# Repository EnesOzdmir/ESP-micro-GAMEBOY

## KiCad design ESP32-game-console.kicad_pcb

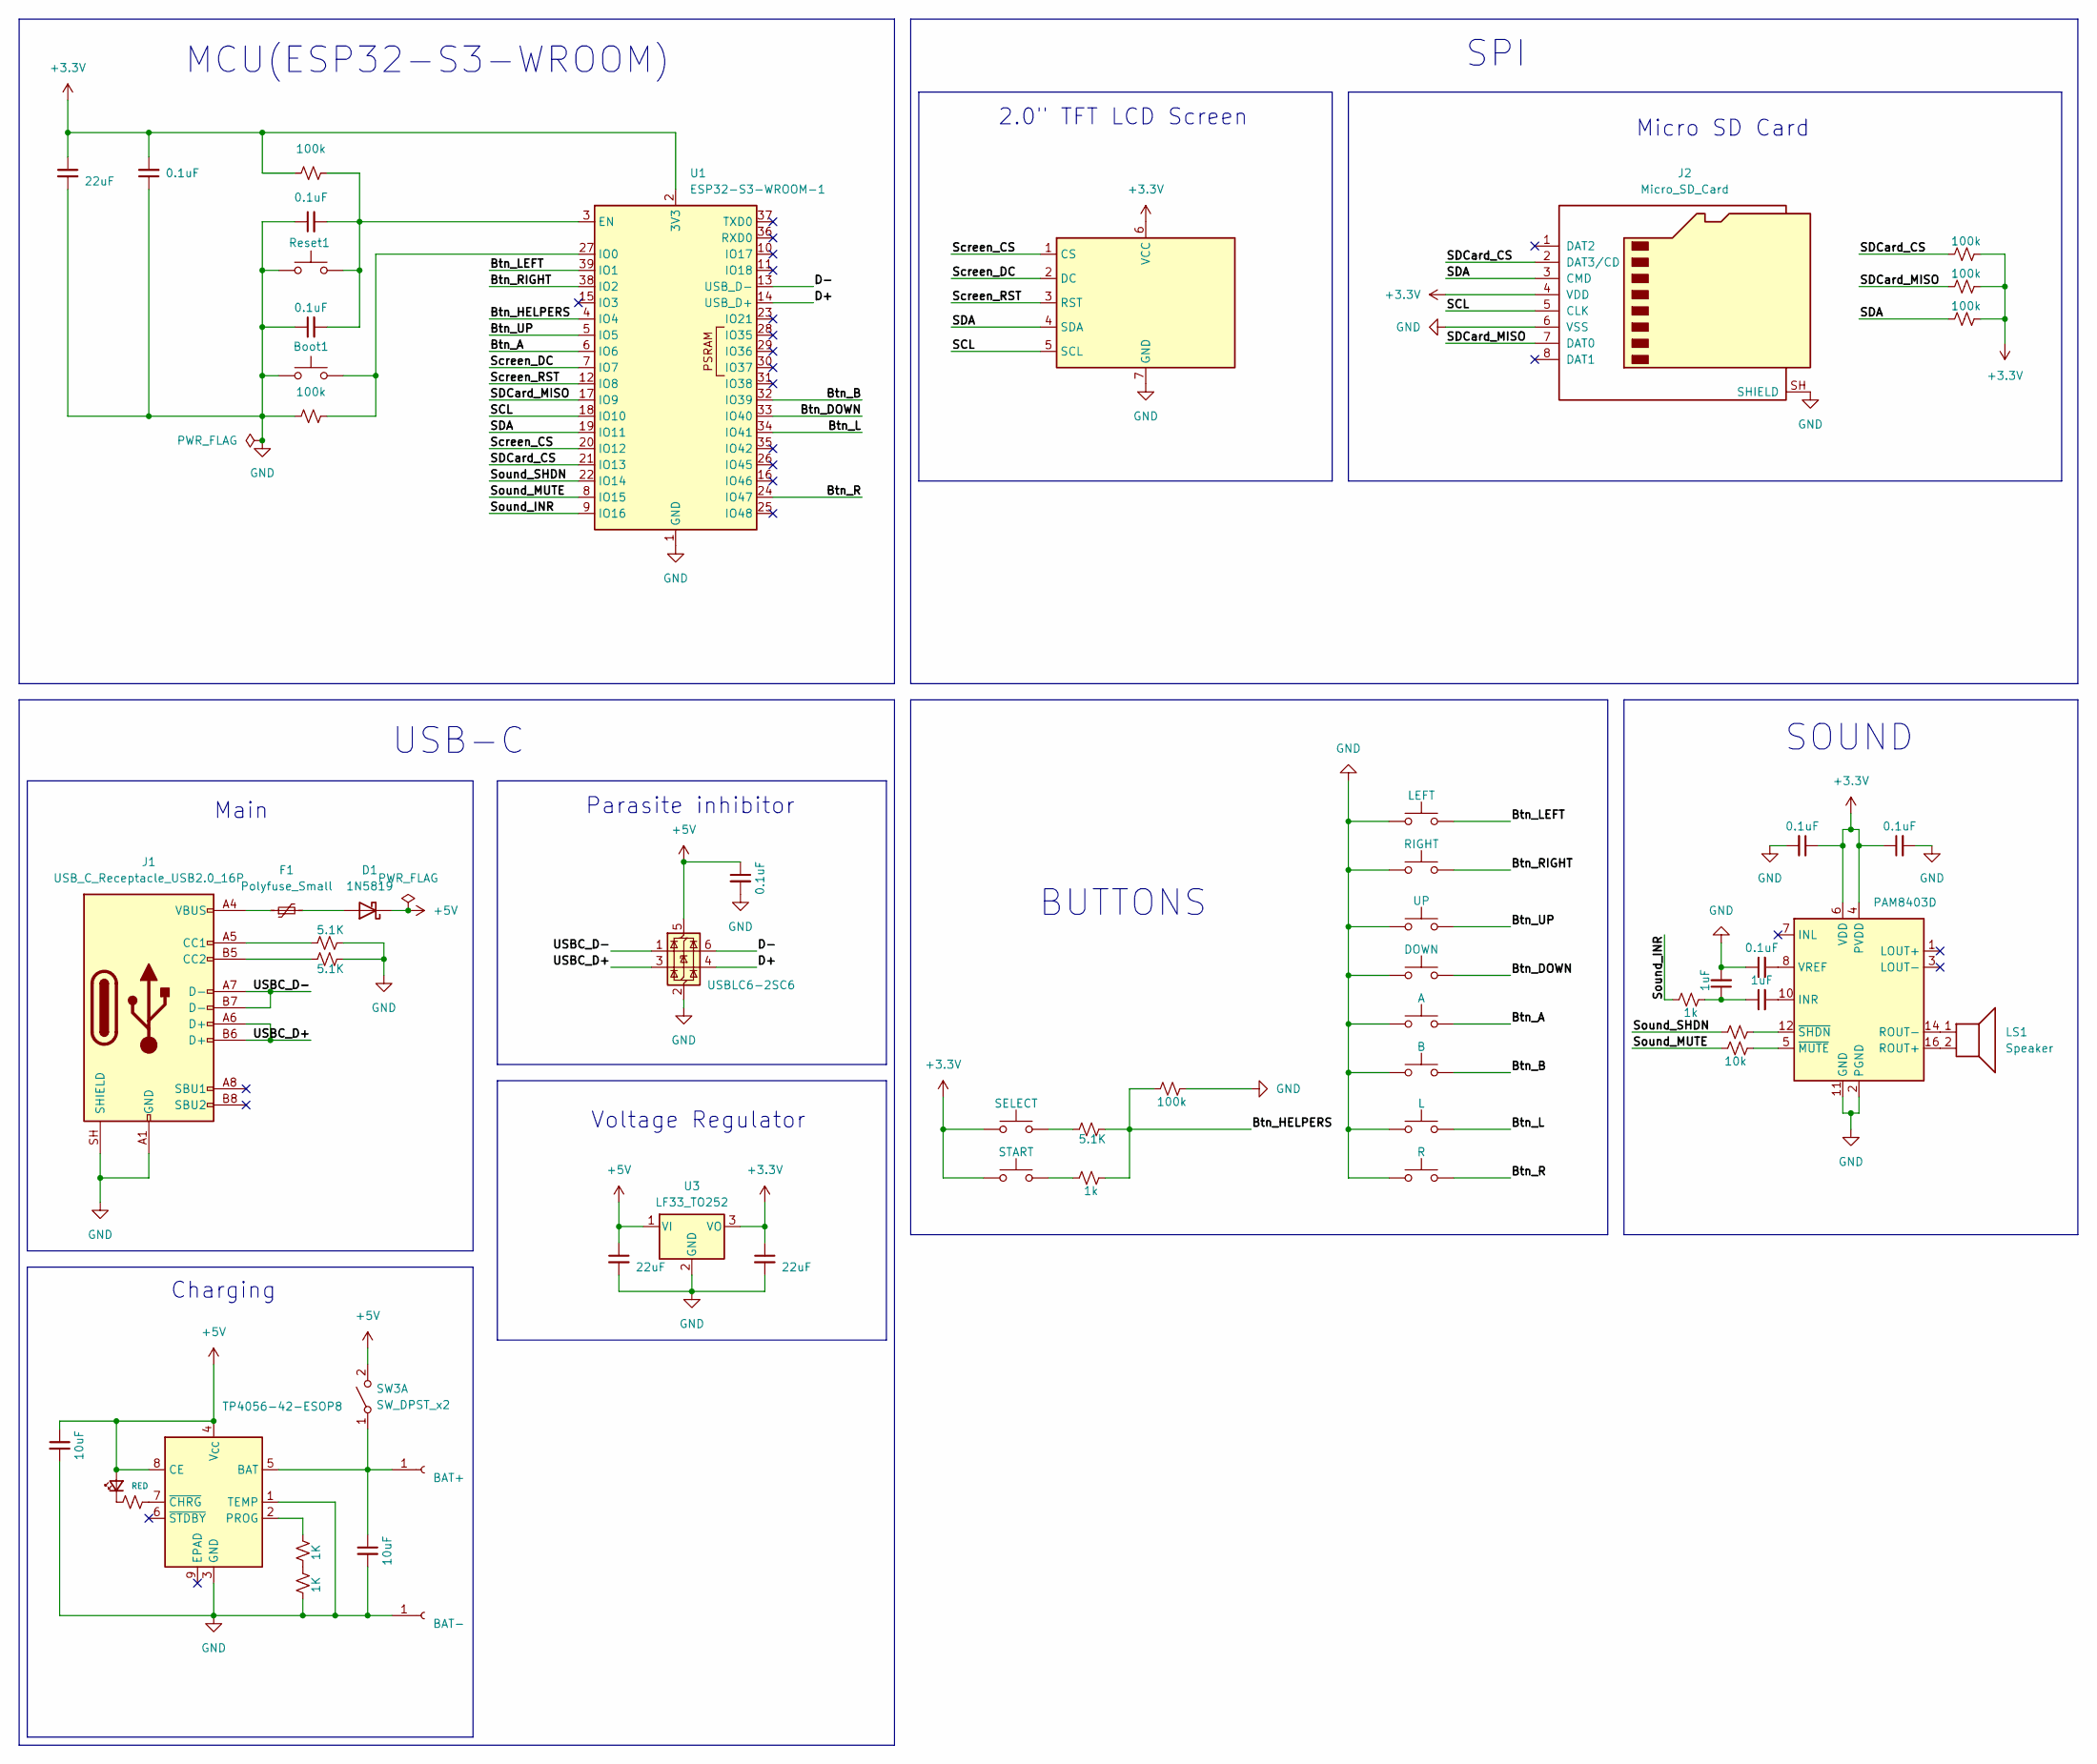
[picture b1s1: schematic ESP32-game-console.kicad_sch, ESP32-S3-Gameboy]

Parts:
Boot1: SW_Push; DS1042-07-1-1KRR16008
C1, C6, C7: 22uF; C_0805_2012Metric_Pad1.18x1.45mm_HandSolder
C2, C3, C4, C10, C11, C12: 0.1uF; C_0805_2012Metric_Pad1.18x1.45mm_HandSolder
C5: 0.1uF; C_0805_2012Metric
C8, C9: 10uF; C_0805_2012Metric_Pad1.18x1.45mm_HandSolder
C13, C14: 1uF; C_0805_2012Metric_Pad1.18x1.45mm_HandSolder
D1: 1N5819; D_DO-41_SOD81_P10.16mm_Horizontal
D3: RED; LED_D3.0mm
F1: Polyfuse_Small; C_Disc_D7.0mm_W2.5mm_P5.00mm
J1: USB_C_Receptacle_USB2.0_16P; USB_C_Receptacle_HRO_TYPE-C-31-M-12
J2: Micro_SD_Card; microSD_HC_Hirose_DM3AT-SF-PEJM5
J3: BAT+; SolderWire-0.75sqmm_1x01_D1.25mm_OD3.5mm
J4: BAT-; SolderWire-0.75sqmm_1x01_D1.25mm_OD3.5mm
LS1: Speaker; TestPoint_2Pads_Pitch5.08mm_Drill1.3mm
R1, R2, R8, R9, R10, R14: 100k; R_0805_2012Metric_Pad1.20x1.40mm_HandSolder
R3, R4, R5: 5.1K; R_0805_2012Metric_Pad1.20x1.40mm_HandSolder
R7, R11, R16: 1K; R_0805_2012Metric_Pad1.20x1.40mm_HandSolder
R13, R15: 1k; R_0805_2012Metric_Pad1.20x1.40mm_HandSolder
R17, R18: 10k; R_Axial_DIN0207_L6.3mm_D2.5mm_P10.16mm_Horizontal
Reset1: SW_Push; DS1042-07-1-1KRR16008
SW1: LEFT; SW_TH_Tactile_Omron_B3F-100x
SW2: RIGHT; SW_TH_Tactile_Omron_B3F-100x
SW3: SW_DPST_x2; L-KLS7-MSK-12C03
SW7: UP; SW_TH_Tactile_Omron_B3F-100x
SW8: DOWN; SW_TH_Tactile_Omron_B3F-100x
SW9: A; SW_TH_Tactile_Omron_B3F-100x
SW10: B; SW_TH_Tactile_Omron_B3F-100x
SW11: L; L-KLS7-TS3609-1.8-160-T
SW12: R; L-KLS7-TS3609-1.8-160-T
SW18: SELECT; L-KLS7-TS3609-1.8-160-T
SW19: START; L-KLS7-TS3609-1.8-160-T
U1: ESP32-S3-WROOM-1; ESP32-S3-WROOM-1U
U2: USBLC6-2SC6; SOT-23-6
U3: LF33_TO252; TO-252-2
U4: TP4056-42-ESOP8; SOIC-8-1EP_3.9x4.9mm_P1.27mm_EP2.29x3mm_ThermalVias
U5: ST7789V
U6: PAM8403D; SOIC-16_3.9x9.9mm_P1.27mm

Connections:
+3.3V: C1.1, C2.2, C7.1, C10.1, C11.1, J2.4 (VDD), R1.1, R8.2, R9.2, R10.2, SW18.1, SW19.1, U1.2 (3V3), U3.3 (VO), U5.6 (VCC), U6.4 (PVDD), U6.6 (VDD), U6.13 (PVDD)
+5V: C5.1, C6.1, C8.1, D1.1 (K), D3.2 (A), SW3.2 (B), U2.5 (VBUS), U3.1 (VI), U4.4 (V_{CC}), U4.8 (CE)
/Btn_A: SW9.2, U1.6 (IO6)
/Btn_B: SW10.2, U1.32 (IO39)
/Btn_DOWN: SW8.2, U1.33 (IO40)
/Btn_HELPERS: R5.2, R13.2, R14.1, U1.4 (IO4)
/Btn_L: SW11.2, U1.34 (IO41)
/Btn_LEFT: SW1.2, U1.39 (IO1)
/Btn_R: SW12.2, U1.24 (IO47)
/Btn_RIGHT: SW2.2, U1.38 (IO2)
/Btn_UP: SW7.2, U1.5 (IO5)
/D+: U1.14 (USB_D+), U2.4 (I/O2)
/D-: U1.13 (USB_D-), U2.6 (I/O1)
/SCL: J2.5 (CLK), U1.18 (IO10), U5.5 (SCL)
/SDA: J2.3 (CMD), R8.1, U1.19 (IO11), U5.4 (SDA)
/SDCard_CS: J2.2 (DAT3/CD), R10.1, U1.21 (IO13)
/SDCard_MISO: J2.7 (DAT0), R9.1, U1.17 (IO9)
/Screen_CS: U1.20 (IO12), U5.1 (CS)
/Screen_DC: U1.7 (IO7), U5.2 (DC)
/Screen_RST: U1.12 (IO8), U5.3 (RST)
/Sound_INR: R15.1, U1.9 (IO16)
/Sound_MUTE: R18.1, U1.8 (IO15)
/Sound_SHDN: R17.1, U1.22 (IO14)
/USBC_D+: J1.A6 (D+), J1.B6 (D+), U2.3 (I/O2)
/USBC_D-: J1.A7 (D-), J1.B7 (D-), U2.1 (I/O1)
GND: Boot1.1, C1.2, C2.1, C3.1, C4.1, C5.2, C6.2, C7.2, C8.2, C9.2, C10.2, C11.2, C12.1, C14.2, J1.A1 (GND), J1.A12 (GND), J1.B1 (GND), J1.B12 (GND), J1.SH (SHIELD), J2.6 (VSS), J2.SH (SHIELD), J4.1 (Pin_1_1), R2.1, R3.2, R4.2, R14.2, R16.1, Reset1.1, SW1.1, SW2.1, SW7.1, SW8.1, SW9.1, SW10.1, SW11.1, SW12.1, U1.1 (GND), U1.40 (GND), U1.41 (GND), U2.2 (GND), U3.2 (GND), U4.1 (TEMP), U4.3 (GND), U5.7 (GND), U6.2 (PGND), U6.11 (GND), U6.15 (PGND)
unnamed: C13.1, C14.1, R15.2
unnamed: D1.2 (A), F1.2
unnamed: D3.1 (K), R7.1
unnamed: F1.1, J1.A4 (VBUS), J1.A9 (VBUS), J1.B4 (VBUS), J1.B9 (VBUS)
unnamed: J1.A5 (CC1), R4.1
unnamed: J1.B5 (CC2), R3.1
unnamed: C9.1, J3.1 (Pin_1_1), SW3.1 (A), U4.5 (BAT)
unnamed: R5.1, SW18.2
unnamed: R11.1, R16.2
unnamed: R13.1, SW19.2
unnamed: C3.2, C4.2, R1.2, Reset1.2, U1.3 (EN)
unnamed: Boot1.2, R2.2, U1.27 (IO0)
unnamed: R11.2, U4.2 (PROG)
unnamed: R7.2, U4.7 (~CHRG)
unnamed: C13.2, U6.10 (INR)
unnamed: LS1.2, U6.16 (ROUT+)
unnamed: LS1.1, U6.14 (ROUT-)
unnamed: C12.2, U6.8 (VREF)
unnamed: R18.2, U6.5 (~MUTE)
unnamed: R17.2, U6.12 (~SHDN)

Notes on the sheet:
MCU(ESP32-S3-WROOM)
SPI
USB-C
Micro SD Card
2.0" TFT LCD Screen
Charging
Main
Parasite inhibitor
SOUND
Voltage Regulator
BUTTONS

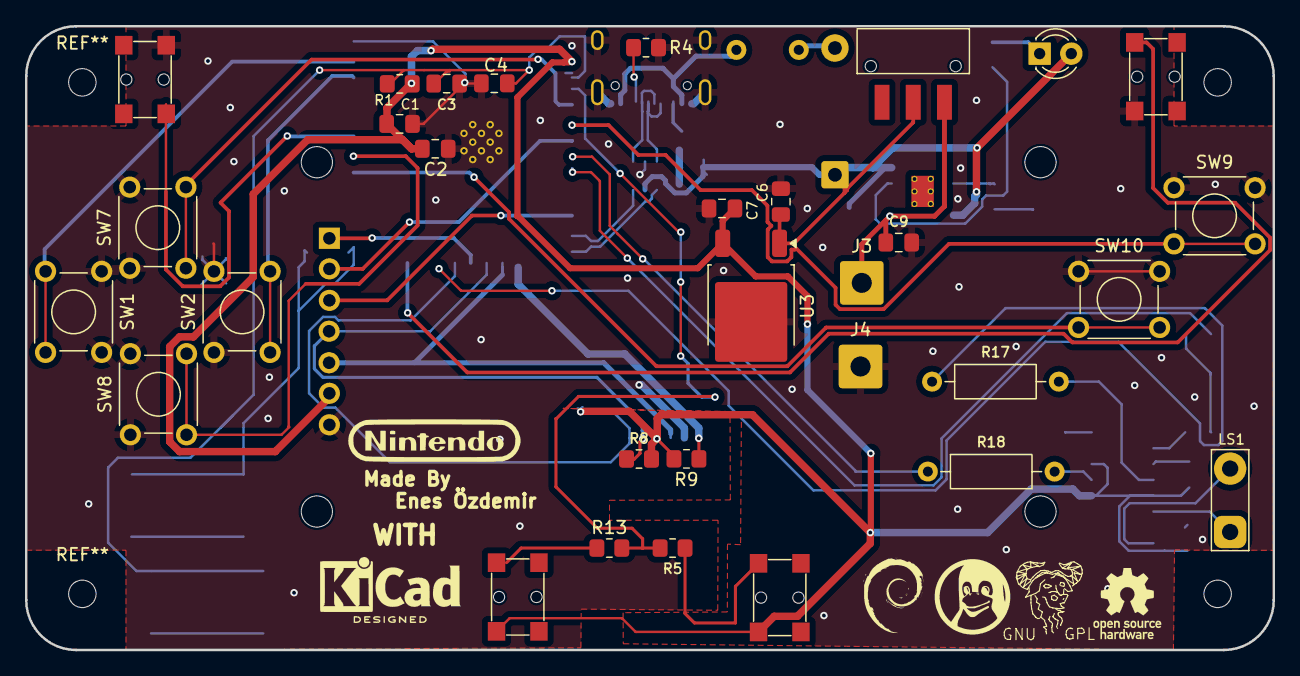
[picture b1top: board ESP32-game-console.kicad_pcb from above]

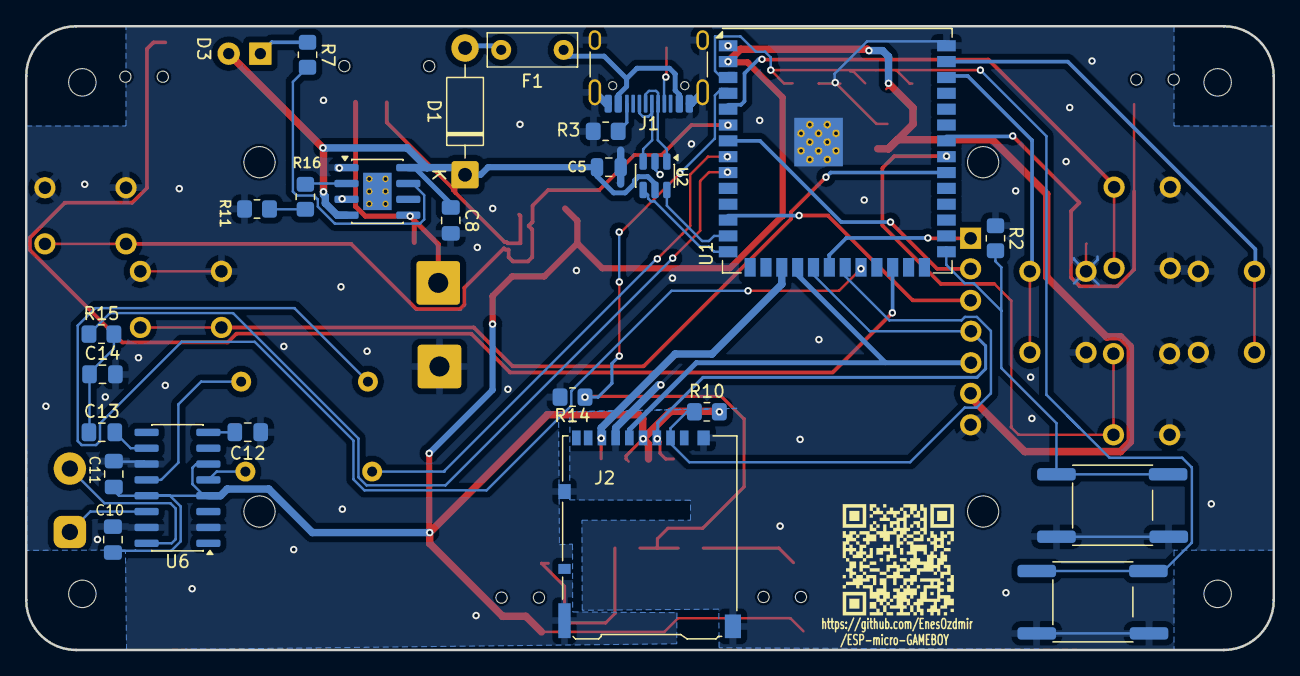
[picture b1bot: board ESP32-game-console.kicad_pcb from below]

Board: 2 copper layers, 100.0 x 50.0 mm, 57 parts (25 on the bottom side), 46 nets.
